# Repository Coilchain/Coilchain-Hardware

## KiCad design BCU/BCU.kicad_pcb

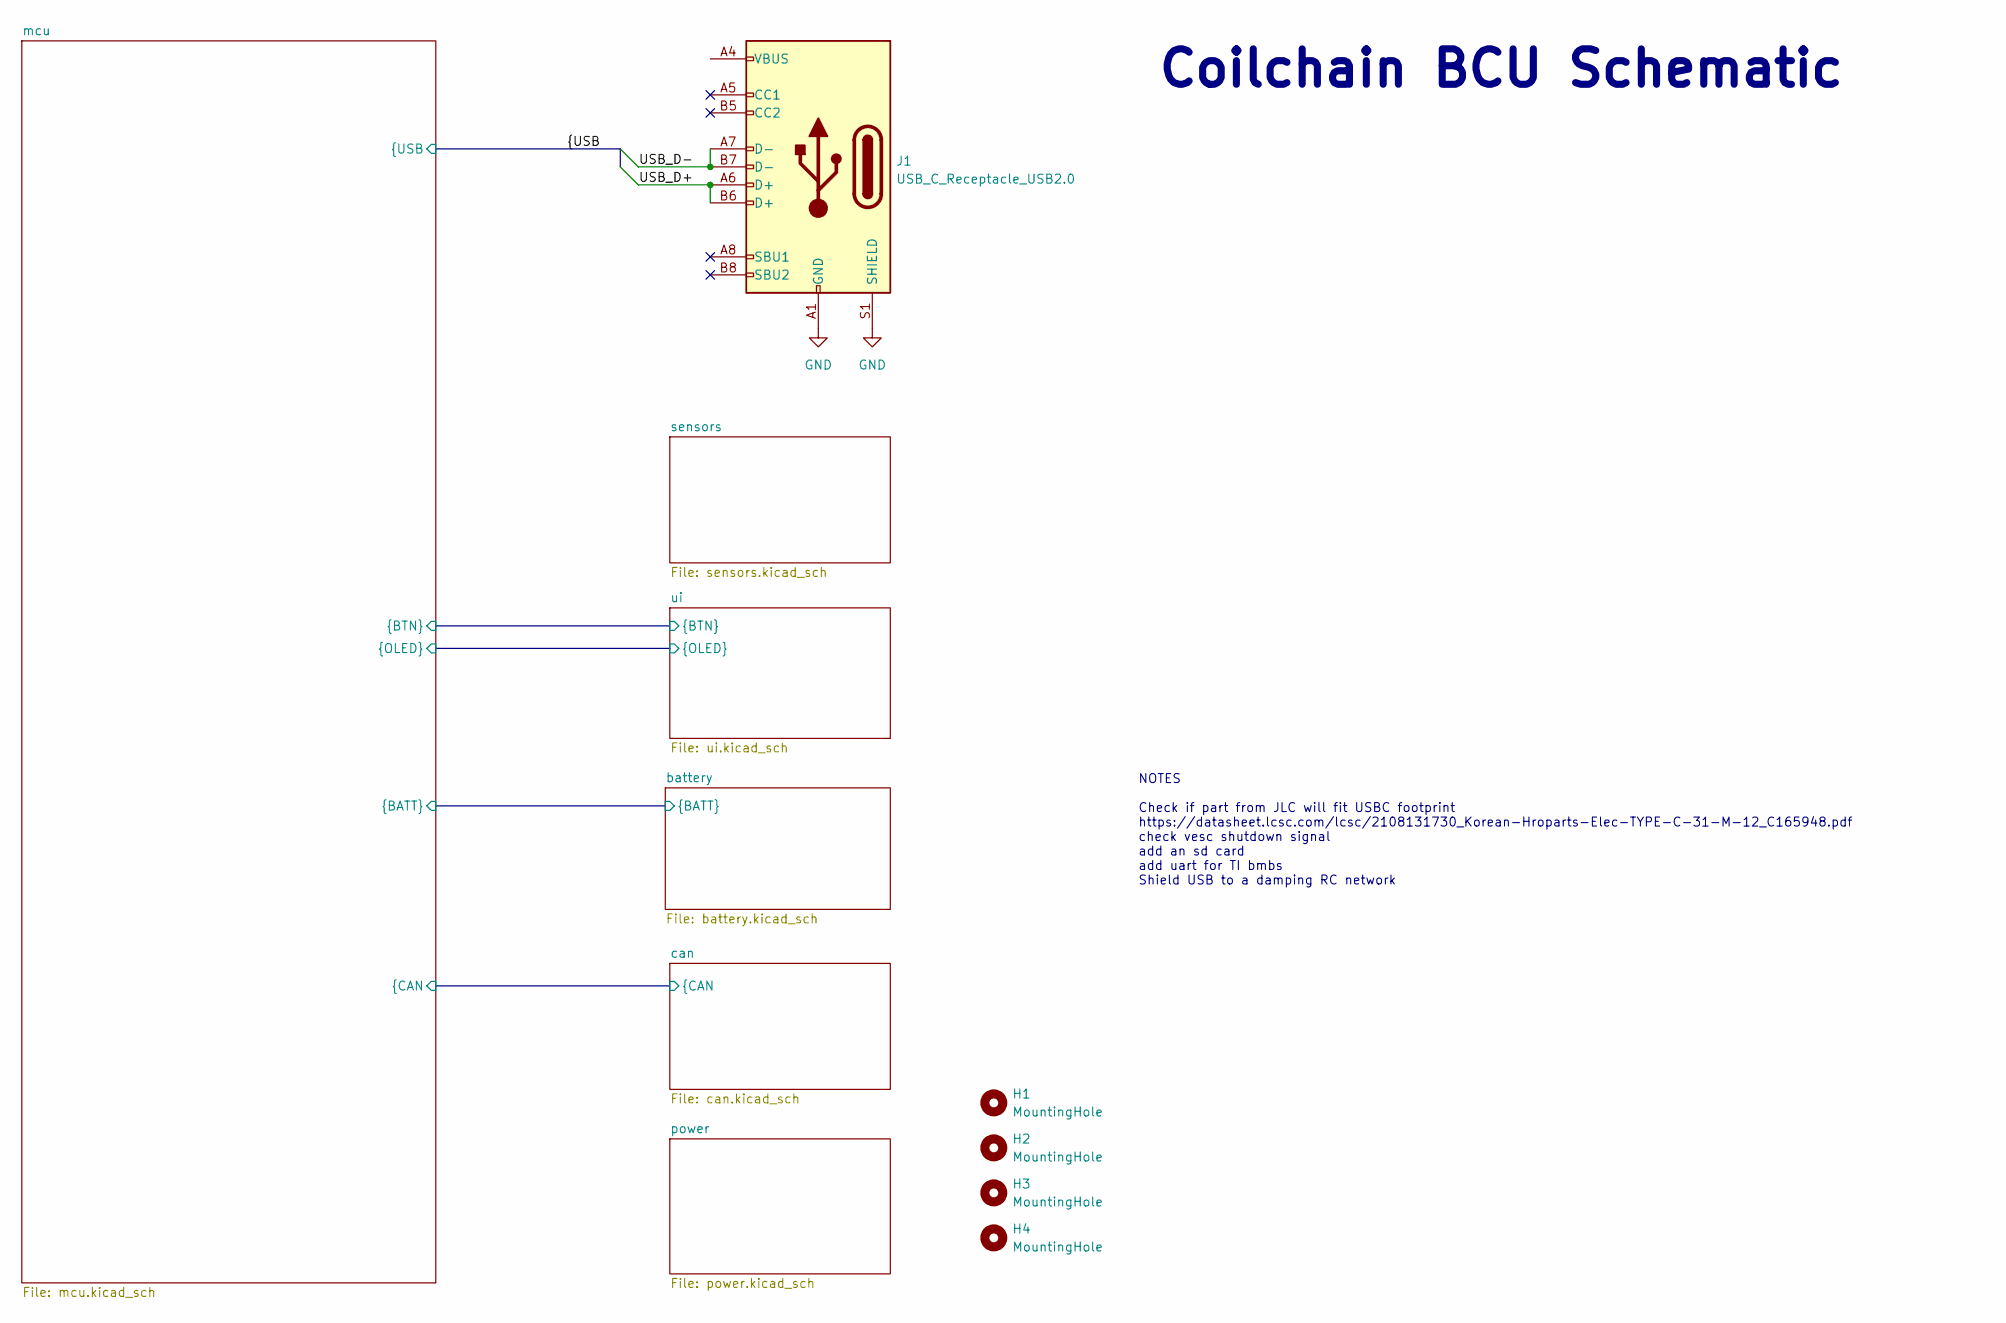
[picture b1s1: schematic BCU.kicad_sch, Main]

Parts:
H1, H2, H3, H4: MountingHole; MountingHole_2.2mm_M2
J1: USB_C_Receptacle_USB2.0; USB_C_Receptacle_HRO_TYPE-C-31-M-12

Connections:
/USB_D+: J1.A6 (D+), J1.B6 (D+)
/USB_D-: J1.A7 (D-), J1.B7 (D-)
GND: J1.A1 (GND), J1.A12 (GND), J1.B1 (GND), J1.B12 (GND), J1.S1 (SHIELD); also elsewhere on the board
unnamed: J1.A4 (VBUS), J1.A9 (VBUS), J1.B4 (VBUS), J1.B9 (VBUS)

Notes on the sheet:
Coilchain BCU Schematic
NOTES Check if part from JLC will fit USBC footprint https://datasheet.lcsc.com/lcsc/2108131730_Korean-Hroparts-Elec-TYPE-C-31-M-12_C165948.pdf check vesc shutdown signal add an sd card add uart for TI bmbs Shield USB to a damping RC network

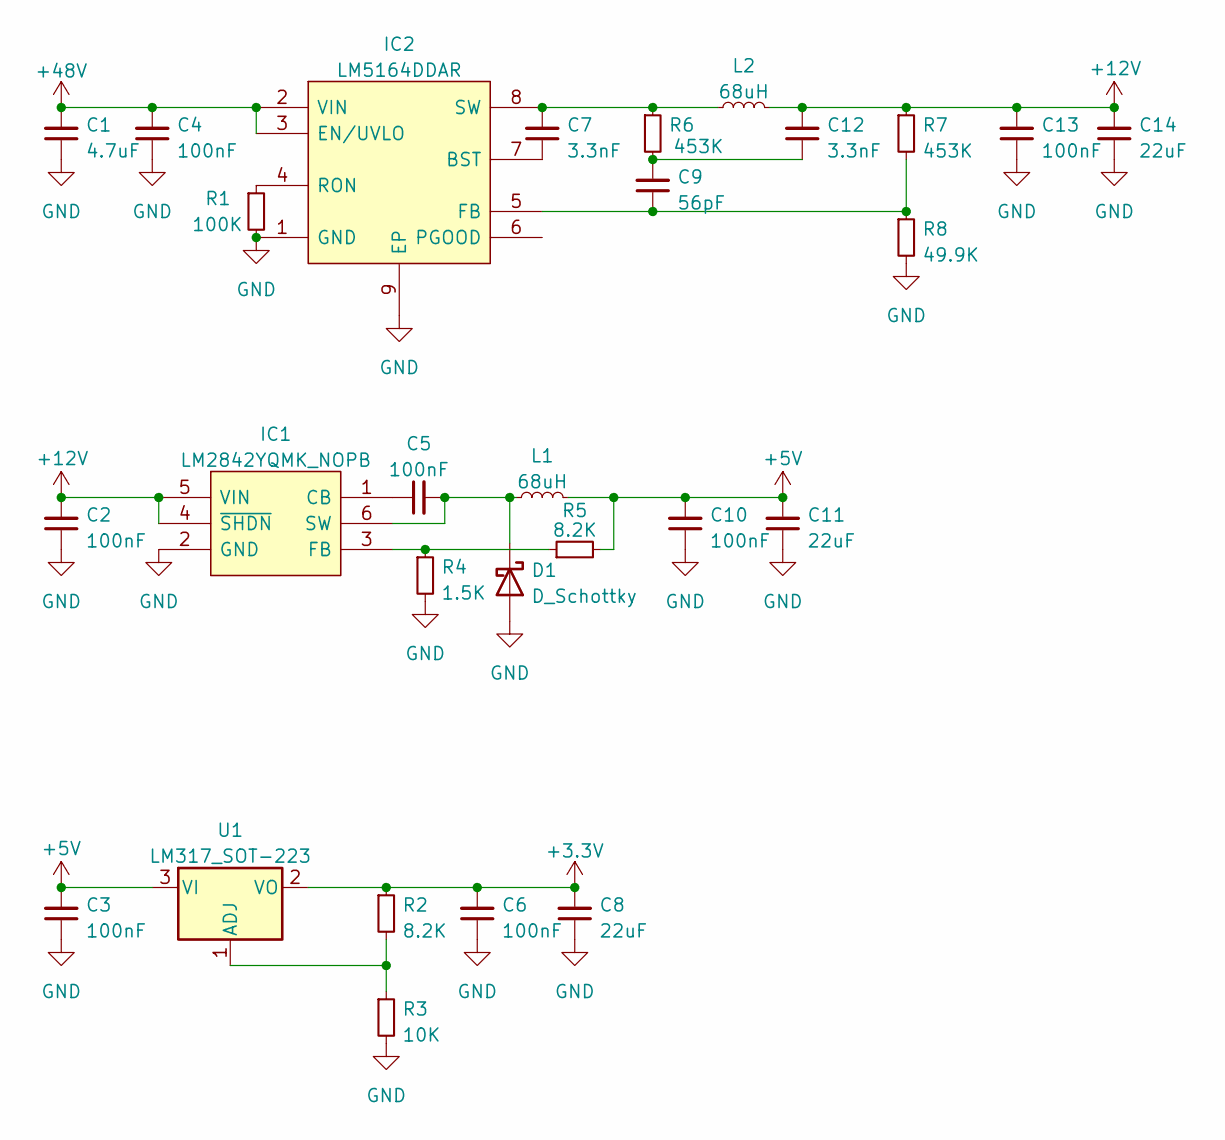
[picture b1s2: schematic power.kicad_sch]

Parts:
C1: 4.7uF; C_0603_1608Metric_Pad1.08x0.95mm_HandSolder
C2, C3, C4, C5, C6, C10, C13: 100nF; C_0402_1005Metric_Pad0.74x0.62mm_HandSolder
C7, C12: 3.3nF; C_0402_1005Metric_Pad0.74x0.62mm_HandSolder
C8, C11, C14: 22uF; C_0805_2012Metric_Pad1.18x1.45mm_HandSolder
C9: 56pF; C_0402_1005Metric_Pad0.74x0.62mm_HandSolder
D1: D_Schottky
IC1: LM2842YQMK_NOPB; SuperSOT-6; Manufacturer_Part_Number LM2842YQMK/NOPB; Mouser Part Number 926-LM2842YQMK/NOPB
IC2: LM5164DDAR; Texas_R-PDSO-G8_EP2.95x4.9mm_Mask2.4x3.1mm_ThermalVias; Manufacturer_Part_Number LM5164DDAR; Mouser Part Number 595-LM5164DDAR
L1: 68uH; L_1210_3225Metric_Pad1.42x2.65mm_HandSolder
L2: 68uH; L_TDK_SLF7045
R1: 100K; R_0402_1005Metric_Pad0.72x0.64mm_HandSolder
R2, R5: 8.2K; R_0402_1005Metric_Pad0.72x0.64mm_HandSolder
R3: 10K; R_0402_1005Metric_Pad0.72x0.64mm_HandSolder
R4: 1.5K; R_0402_1005Metric_Pad0.72x0.64mm_HandSolder
R6, R7: 453K; R_0402_1005Metric_Pad0.72x0.64mm_HandSolder
R8: 49.9K; R_0402_1005Metric_Pad0.72x0.64mm_HandSolder
U1: LM317_SOT-223; SOT-223-3_TabPin2

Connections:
+3V3: C6.2, C8.2, R2.1, U1.2 (VO); also elsewhere on the board
+5V: C3.2, C10.2, C11.2, L1.2, R5.2, U1.3 (VI); also elsewhere on the board
+12V: C2.2, C12.2, C13.2, C14.2, IC1.4 (~SHDN), IC1.5 (VIN), L2.2, R7.1
+48V: C1.2, C4.2, IC2.2 (VIN), IC2.3 (EN/UVLO)
GND: C1.1, C2.1, C3.1, C4.1, C6.1, C8.1, C10.1, C11.1, C13.1, C14.1, D1.2 (A), IC1.2 (GND), IC2.1 (GND), IC2.9 (EP), R1.2, R3.2, R4.2, R8.2; also elsewhere on the board
unnamed: C5.1, IC1.1 (CB)
unnamed: C5.2, D1.1 (K), IC1.6 (SW), L1.1
unnamed: C7.1, IC2.7 (BST)
unnamed: C7.2, IC2.8 (SW), L2.1, R6.1
unnamed: C9.1, IC2.5 (FB), R7.2, R8.1
unnamed: C9.2, C12.1, R6.2
unnamed: IC2.4 (RON), R1.1
unnamed: R2.2, R3.1, U1.1 (ADJ)
unnamed: IC1.3 (FB), R4.1, R5.1

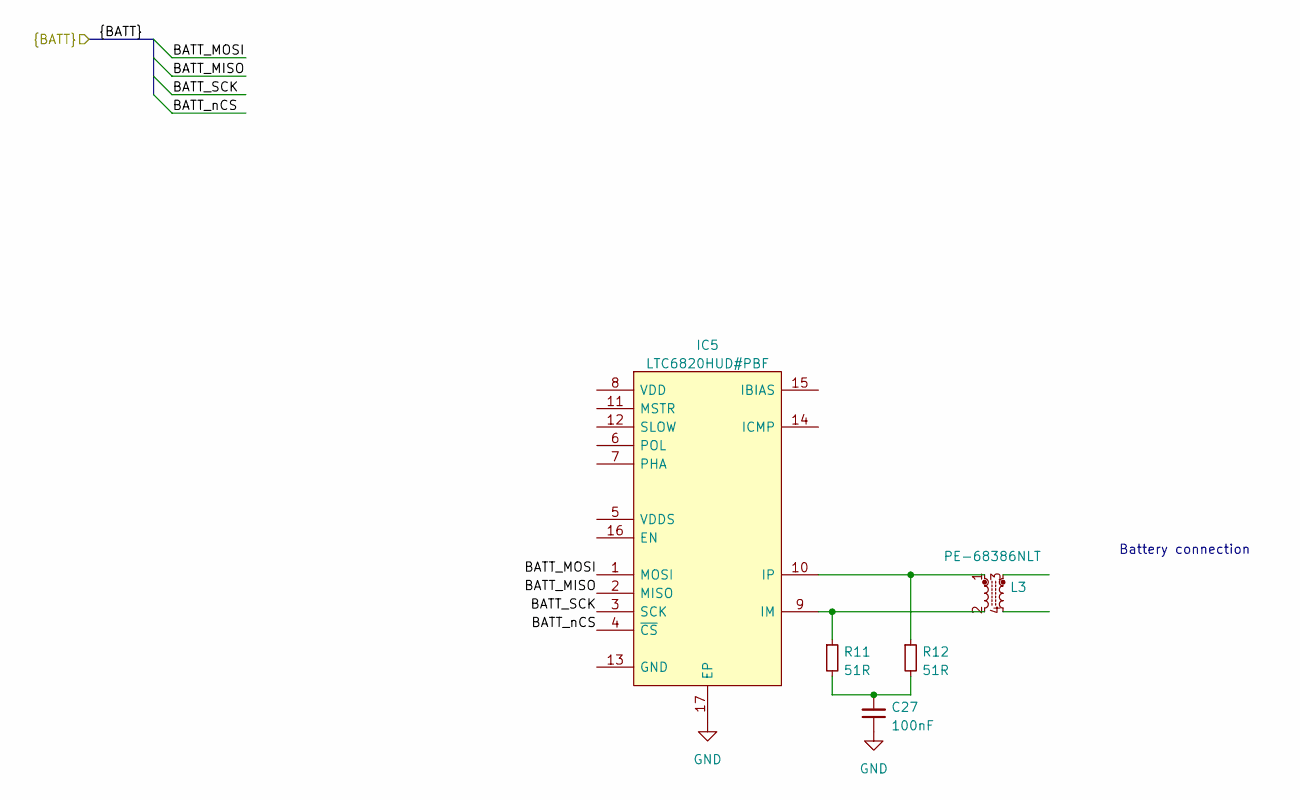
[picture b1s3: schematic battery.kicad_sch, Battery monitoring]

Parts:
C27: 100nF; C_0402_1005Metric_Pad0.74x0.62mm_HandSolder
IC5: LTC6820HUD#PBF; QFN-16-1EP_3x3mm_P0.5mm_EP1.7x1.7mm; Manufacturer_Part_Number LTC6820HUD#PBF; Mouser Part Number 584-LTC6820HUD#PBF
L3: PE-68386NLT
R11, R12: 51R; R_0402_1005Metric_Pad0.72x0.64mm_HandSolder

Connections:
/battery/BATT_MISO: IC5.2 (MISO)
/battery/BATT_MOSI: IC5.1 (MOSI)
/battery/BATT_SCK: IC5.3 (SCK)
/battery/BATT_nCS: IC5.4 (~CS)
GND: C27.1, IC5.17 (EP); also elsewhere on the board
unnamed: C27.2, R11.2, R12.2
unnamed: IC5.9 (IM), L3.2, R11.1
unnamed: IC5.10 (IP), L3.1, R12.1

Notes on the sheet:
Battery connection

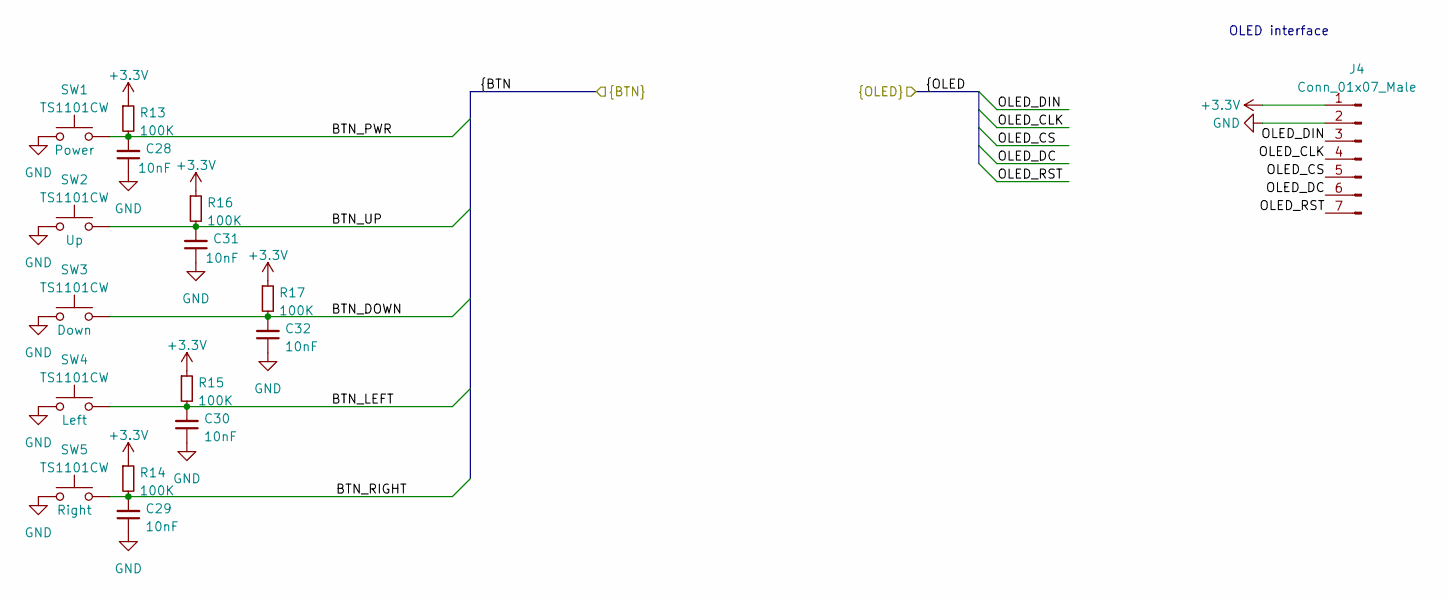
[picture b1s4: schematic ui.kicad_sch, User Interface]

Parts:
C28, C29, C30, C31, C32: 10nF; C_0402_1005Metric_Pad0.74x0.62mm_HandSolder
J4: Conn_01x07_Male; PinHeader_1x07_P2.54mm_Vertical
R13, R14, R15, R16, R17: 100K; R_0402_1005Metric_Pad0.72x0.64mm_HandSolder
SW1, SW2, SW3, SW4, SW5: TS1101CW; TS-1101-C-W

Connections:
+3V3: J4.1, R13.1, R14.1, R15.1, R16.1, R17.1; also elsewhere on the board
/mcu/BTN_DOWN: C32.2, R17.2, SW3.2; also elsewhere on the board
/mcu/BTN_LEFT: C30.2, R15.2, SW4.2; also elsewhere on the board
/mcu/BTN_PWR: C28.2, R13.2, SW1.2; also elsewhere on the board
/mcu/BTN_RIGHT: C29.2, R14.2, SW5.2; also elsewhere on the board
/mcu/BTN_UP: C31.2, R16.2, SW2.2; also elsewhere on the board
/mcu/OLED_CLK: J4.4; also elsewhere on the board
/mcu/OLED_CS: J4.5; also elsewhere on the board
/mcu/OLED_DC: J4.6; also elsewhere on the board
/mcu/OLED_DIN: J4.3; also elsewhere on the board
/mcu/OLED_RST: J4.7; also elsewhere on the board
GND: C28.1, C29.1, C30.1, C31.1, C32.1, J4.2, SW1.1, SW2.1, SW3.1, SW4.1, SW5.1; also elsewhere on the board

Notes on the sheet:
OLED interface

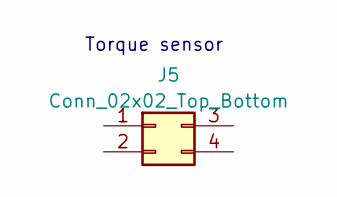
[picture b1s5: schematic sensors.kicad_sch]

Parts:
J5: Conn_02x02_Top_Bottom

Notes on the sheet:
Torque sensor

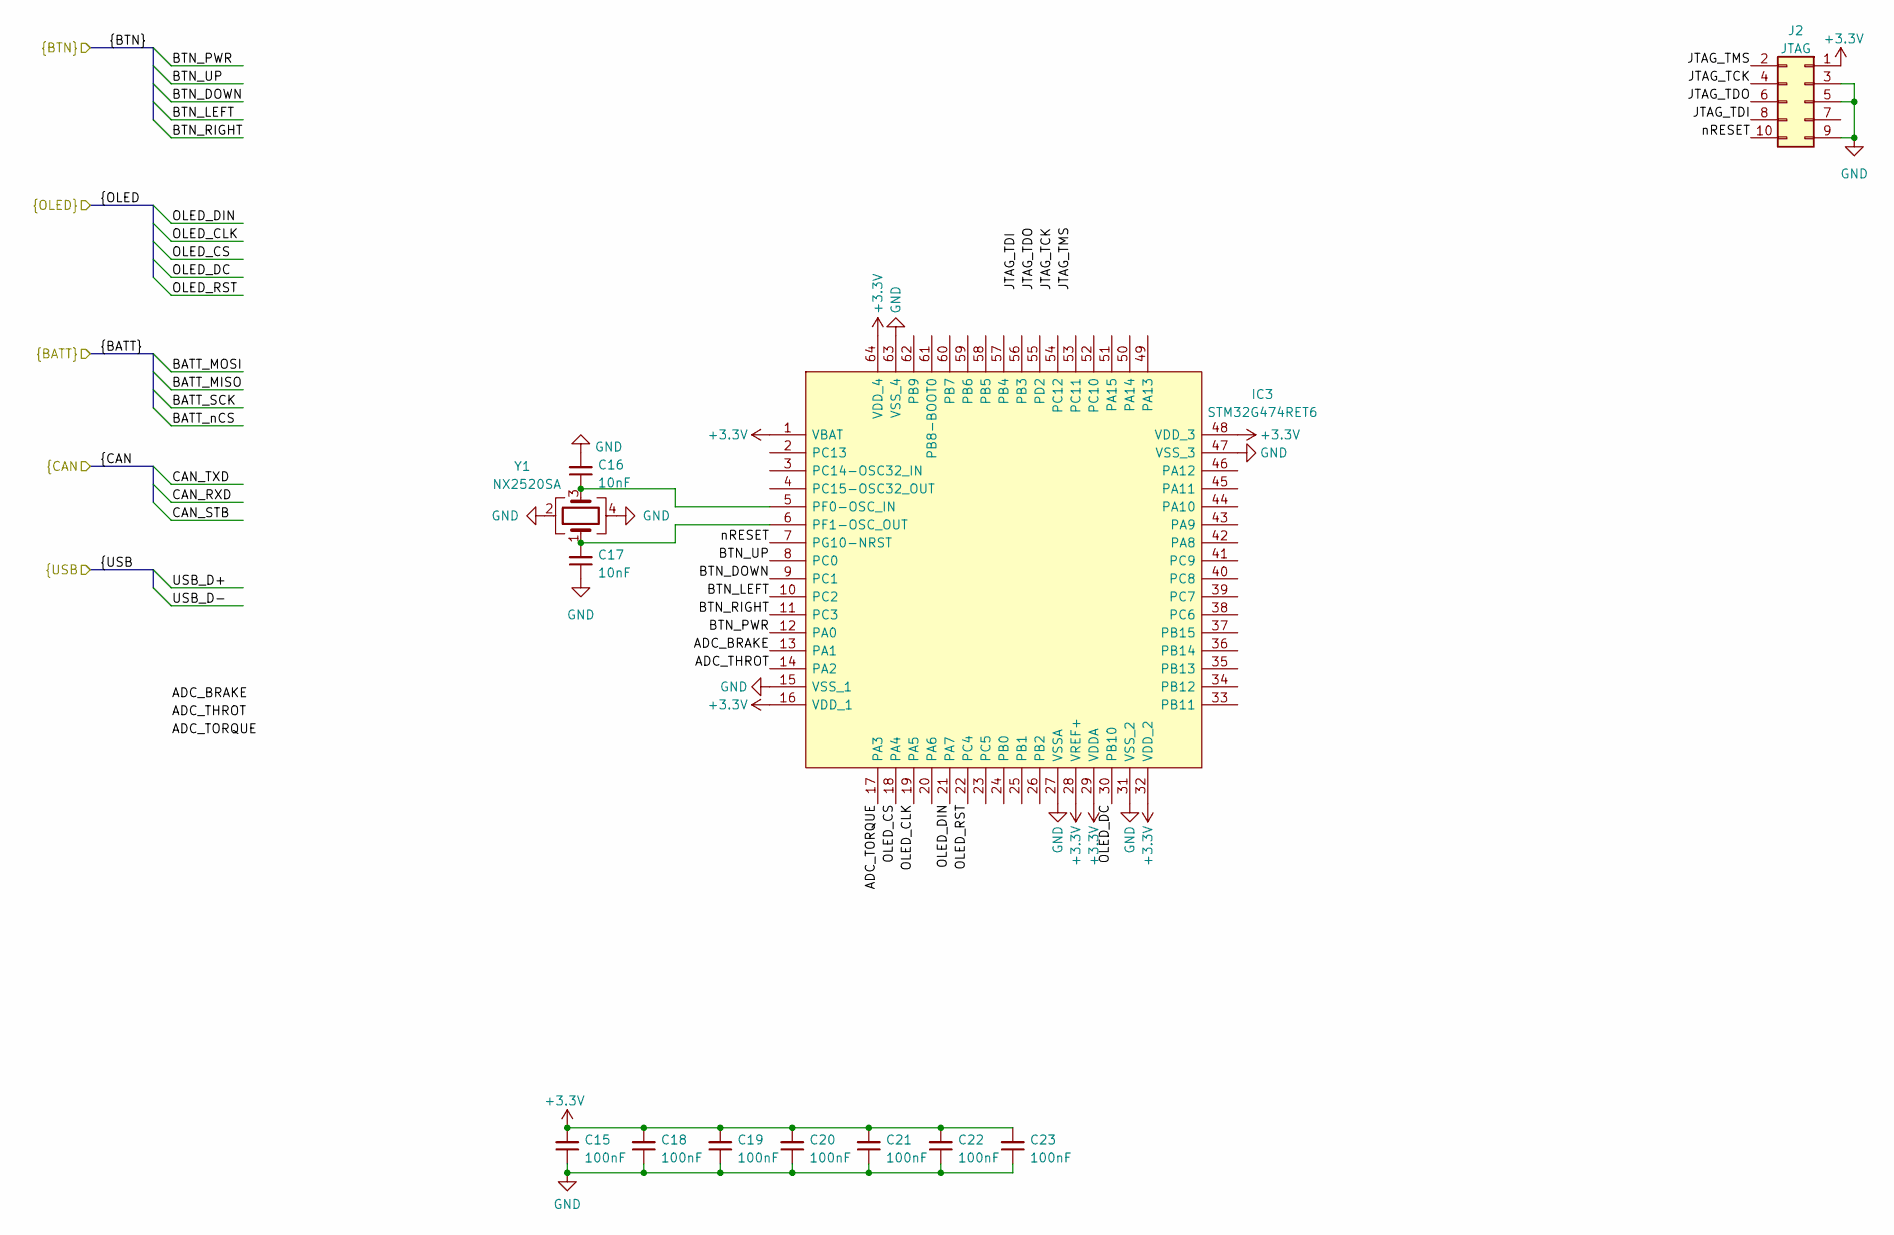
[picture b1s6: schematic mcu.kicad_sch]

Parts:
C15, C18, C19, C20, C21, C22, C23: 100nF; C_0402_1005Metric_Pad0.74x0.62mm_HandSolder
C16, C17: 10nF; C_0402_1005Metric_Pad0.74x0.62mm_HandSolder
IC3: STM32G474RET6; LQFP-64_10x10mm_P0.5mm; Manufacturer_Part_Number STM32G474RET6; Mouser Part Number 511-STM32G474RET6
J2: JTAG; PinHeader_2x05_P1.27mm_Vertical_SMD
Y1: NX2520SA; Crystal_SMD_2520-4Pin_2.5x2.0mm

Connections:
+3V3: C15.2, C18.2, C19.2, C20.2, C21.2, C22.2, C23.2, IC3.1 (VBAT), IC3.16 (VDD_1), IC3.28 (VREF+), IC3.29 (VDDA), IC3.32 (VDD_2), IC3.48 (VDD_3), IC3.64 (VDD_4), J2.1; also elsewhere on the board
/mcu/ADC_BRAKE: IC3.13 (PA1)
/mcu/ADC_THROT: IC3.14 (PA2)
/mcu/ADC_TORQUE: IC3.17 (PA3)
/mcu/BTN_DOWN: IC3.9 (PC1); also elsewhere on the board
/mcu/BTN_LEFT: IC3.10 (PC2); also elsewhere on the board
/mcu/BTN_PWR: IC3.12 (PA0); also elsewhere on the board
/mcu/BTN_RIGHT: IC3.11 (PC3); also elsewhere on the board
/mcu/BTN_UP: IC3.8 (PC0); also elsewhere on the board
/mcu/JTAG_TCK: J2.4
/mcu/JTAG_TDI: J2.8
/mcu/JTAG_TDO: J2.6
/mcu/JTAG_TMS: J2.2
/mcu/OLED_CLK: IC3.19 (PA5); also elsewhere on the board
/mcu/OLED_CS: IC3.18 (PA4); also elsewhere on the board
/mcu/OLED_DC: IC3.30 (PB10); also elsewhere on the board
/mcu/OLED_DIN: IC3.21 (PA7); also elsewhere on the board
/mcu/OLED_RST: IC3.22 (PC4); also elsewhere on the board
/mcu/nRESET: IC3.7 (PG10-NRST), J2.10
GND: C15.1, C16.2, C17.1, C18.1, C19.1, C20.1, C21.1, C22.1, C23.1, IC3.15 (VSS_1), IC3.27 (VSSA), IC3.31 (VSS_2), IC3.47 (VSS_3), IC3.63 (VSS_4), J2.3, J2.5, J2.9, Y1.2, Y1.4; also elsewhere on the board
unnamed: C16.1, IC3.5 (PF0-OSC_IN), Y1.3
unnamed: C17.2, IC3.6 (PF1-OSC_OUT), Y1.1

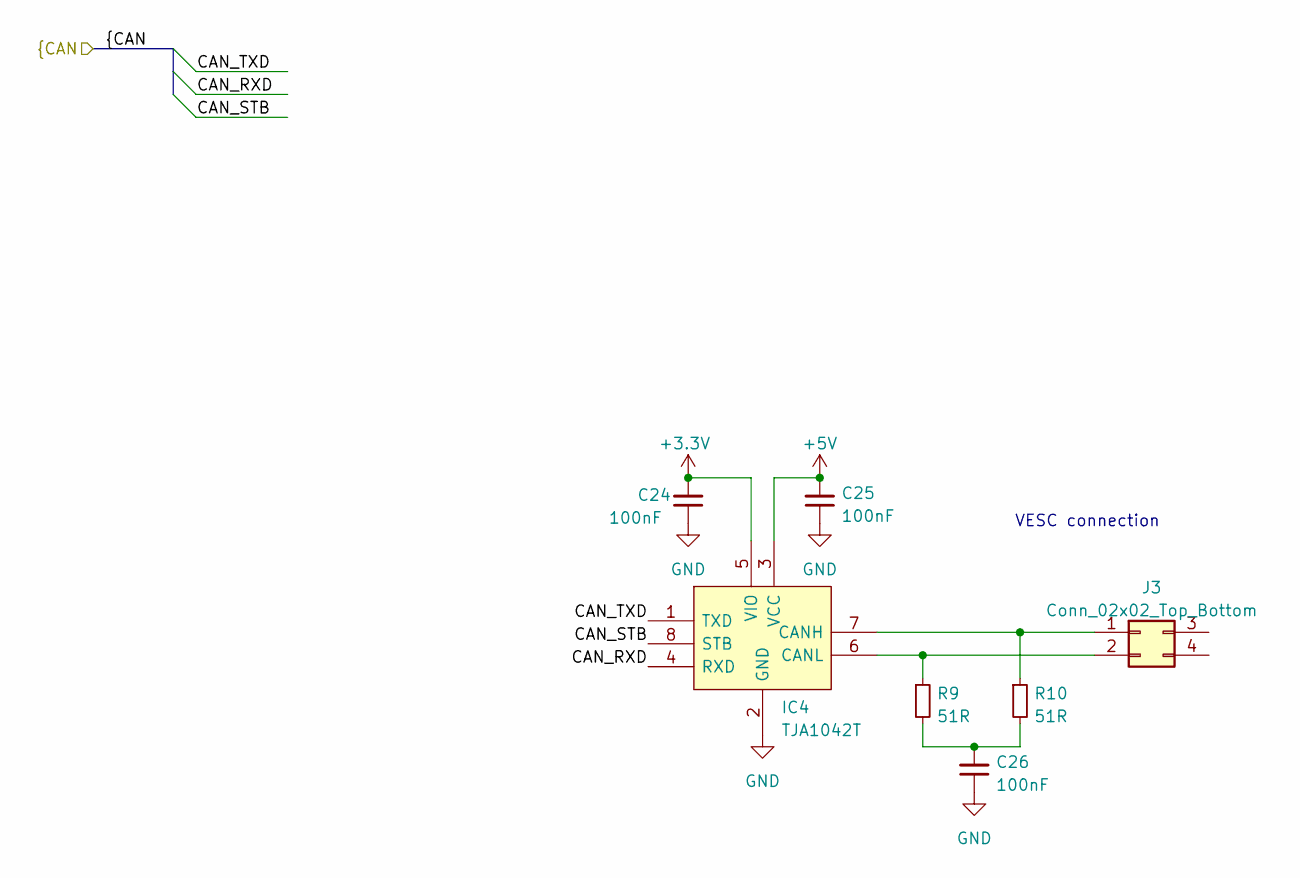
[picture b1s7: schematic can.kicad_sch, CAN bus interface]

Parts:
C24, C25, C26: 100nF; C_0402_1005Metric_Pad0.74x0.62mm_HandSolder
IC4: TJA1042T; SO-8_3.9x4.9mm_P1.27mm; Manufacturer_Part_Number TJA1042T/3,118; Mouser Part Number 771-TJA1042T3118
J3: Conn_02x02_Top_Bottom
R9, R10: 51R; R_0402_1005Metric_Pad0.72x0.64mm_HandSolder

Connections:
+3V3: C24.2, IC4.5 (VIO); also elsewhere on the board
+5V: C25.2, IC4.3 (VCC); also elsewhere on the board
/can/CAN_RXD: IC4.4 (RXD)
/can/CAN_STB: IC4.8 (STB)
/can/CAN_TXD: IC4.1 (TXD)
GND: C24.1, C25.1, C26.1, IC4.2 (GND); also elsewhere on the board
unnamed: C26.2, R9.2, R10.2
unnamed: IC4.6 (CANL), J3.2, R9.1
unnamed: IC4.7 (CANH), J3.1, R10.1

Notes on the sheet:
VESC connection

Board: 2 copper layers, 70 parts (60 on the bottom side), 36 nets, no tracks yet.

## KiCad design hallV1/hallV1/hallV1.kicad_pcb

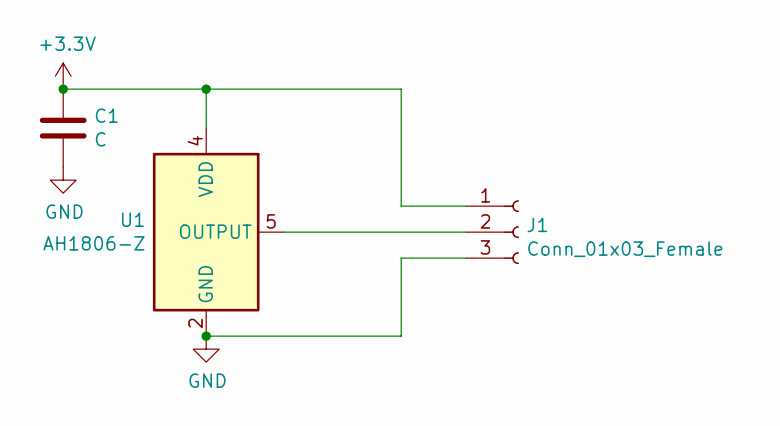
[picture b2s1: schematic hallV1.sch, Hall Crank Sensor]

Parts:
C1: C; C_0603_1608Metric
J1: Conn_01x03_Female; PinHeader_1x03_P2.54mm_Horizontal
U1: AH1806-Z; SOT-553

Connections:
+3V3: C1.1, J1.1, U1.4 (VDD)
GND: C1.2, J1.3, U1.2 (GND)
unnamed: J1.2, U1.5 (OUTPUT)

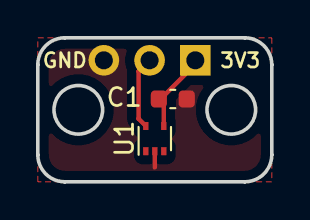
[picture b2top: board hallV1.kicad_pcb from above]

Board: 2 copper layers, 13.0 x 8.0 mm, 3 parts (1 on the bottom side), 3 nets.

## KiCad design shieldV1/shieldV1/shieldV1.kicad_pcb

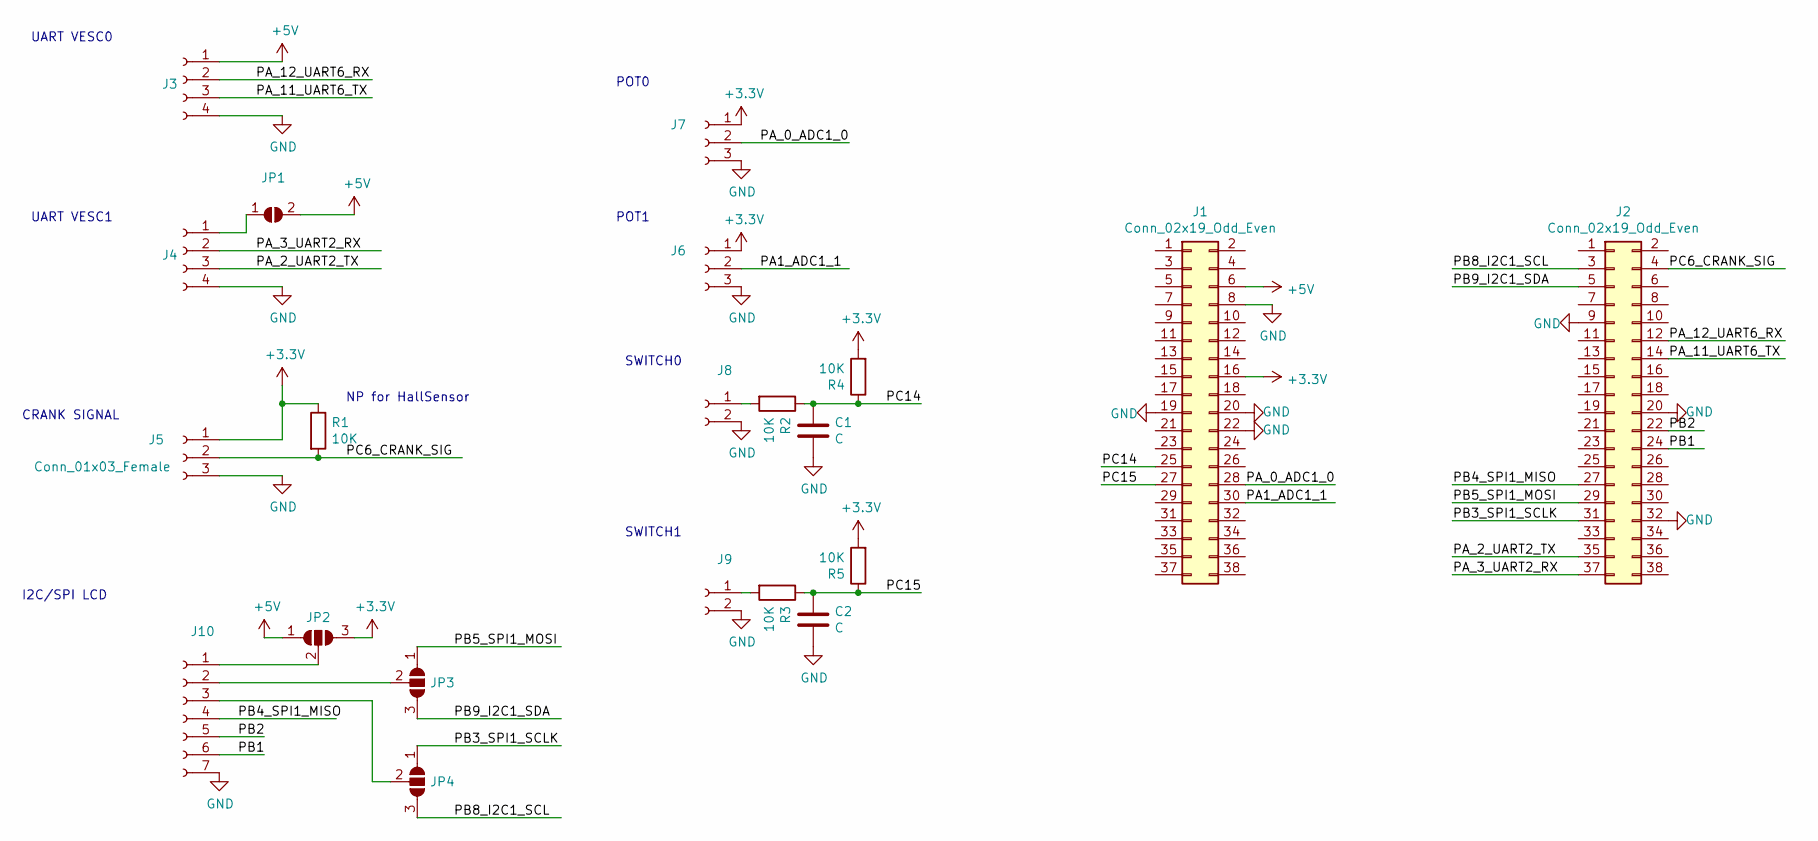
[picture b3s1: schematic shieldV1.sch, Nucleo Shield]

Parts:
C1, C2: C; C_0603_1608Metric
J1, J2: Conn_02x19_Odd_Even; PinSocket_2x19_P2.54mm_Vertical
J3, J4: Conn_01x04_Female; JST_GH_SM04B-GHS-TB_1x04-1MP_P1.25mm_Horizontal
J5, J6, J7: Conn_01x03_Female; JST_GH_SM03B-GHS-TB_1x03-1MP_P1.25mm_Horizontal
J8, J9: Conn_01x02_Female; JST_GH_SM02B-GHS-TB_1x02-1MP_P1.25mm_Horizontal
J10: Conn_01x07_Female; JST_GH_SM07B-GHS-TB_1x07-1MP_P1.25mm_Horizontal
JP1: SolderJumper_2_Open; SolderJumper-2_P1.3mm_Open_RoundedPad1.0x1.5mm
JP2, JP3, JP4: SolderJumper_3_Open; SolderJumper-3_P1.3mm_Open_RoundedPad1.0x1.5mm
R1, R2, R3, R4, R5: 10K; R_0603_1608Metric

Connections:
+3V3: J1.16, J5.1, J6.1, J7.1, JP2.3 (B), R1.1, R4.2, R5.2
+5V: J1.6, J3.1, JP1.2 (B), JP2.1 (A)
/PA1_ADC1_1: J1.30, J6.2
/PA_0_ADC1_0: J1.28, J7.2
/PA_2_UART2_TX: J2.35, J4.3
/PA_3_UART2_RX: J2.37, J4.2
/PA_11_UART6_TX: J2.14, J3.3
/PA_12_UART6_RX: J2.12, J3.2
/PB1: J2.24, J10.6
/PB2: J2.22, J10.5
/PB3_SPI1_SCLK: J2.31, JP4.1 (A)
/PB4_SPI1_MISO: J2.27, J10.4
/PB5_SPI1_MOSI: J2.29, JP3.1 (A)
/PB8_I2C1_SCL: J2.3, JP4.3 (B)
/PB9_I2C1_SDA: J2.5, JP3.3 (B)
/PC6_CRANK_SIG: J2.4, J5.2, R1.2
/PC14: C1.1, J1.25, R2.1, R4.1
/PC15: C2.1, J1.27, R3.1, R5.1
GND: C1.2, C2.2, J1.8, J1.19, J1.20, J1.22, J2.9, J2.20, J2.32, J3.4, J4.4, J5.3, J6.3, J7.3, J8.2, J9.2, J10.7
unnamed: J4.1, JP1.1 (A)
unnamed: J8.1, R2.2
unnamed: J9.1, R3.2
unnamed: J10.1, JP2.2 (C)
unnamed: J10.2, JP3.2 (C)
unnamed: J10.3, JP4.2 (C)

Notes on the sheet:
UART VESC0
UART VESC1
CRANK SIGNAL
NP for HallSensor
I2C/SPI LCD
SWITCH1
SWITCH0
POT1
POT0

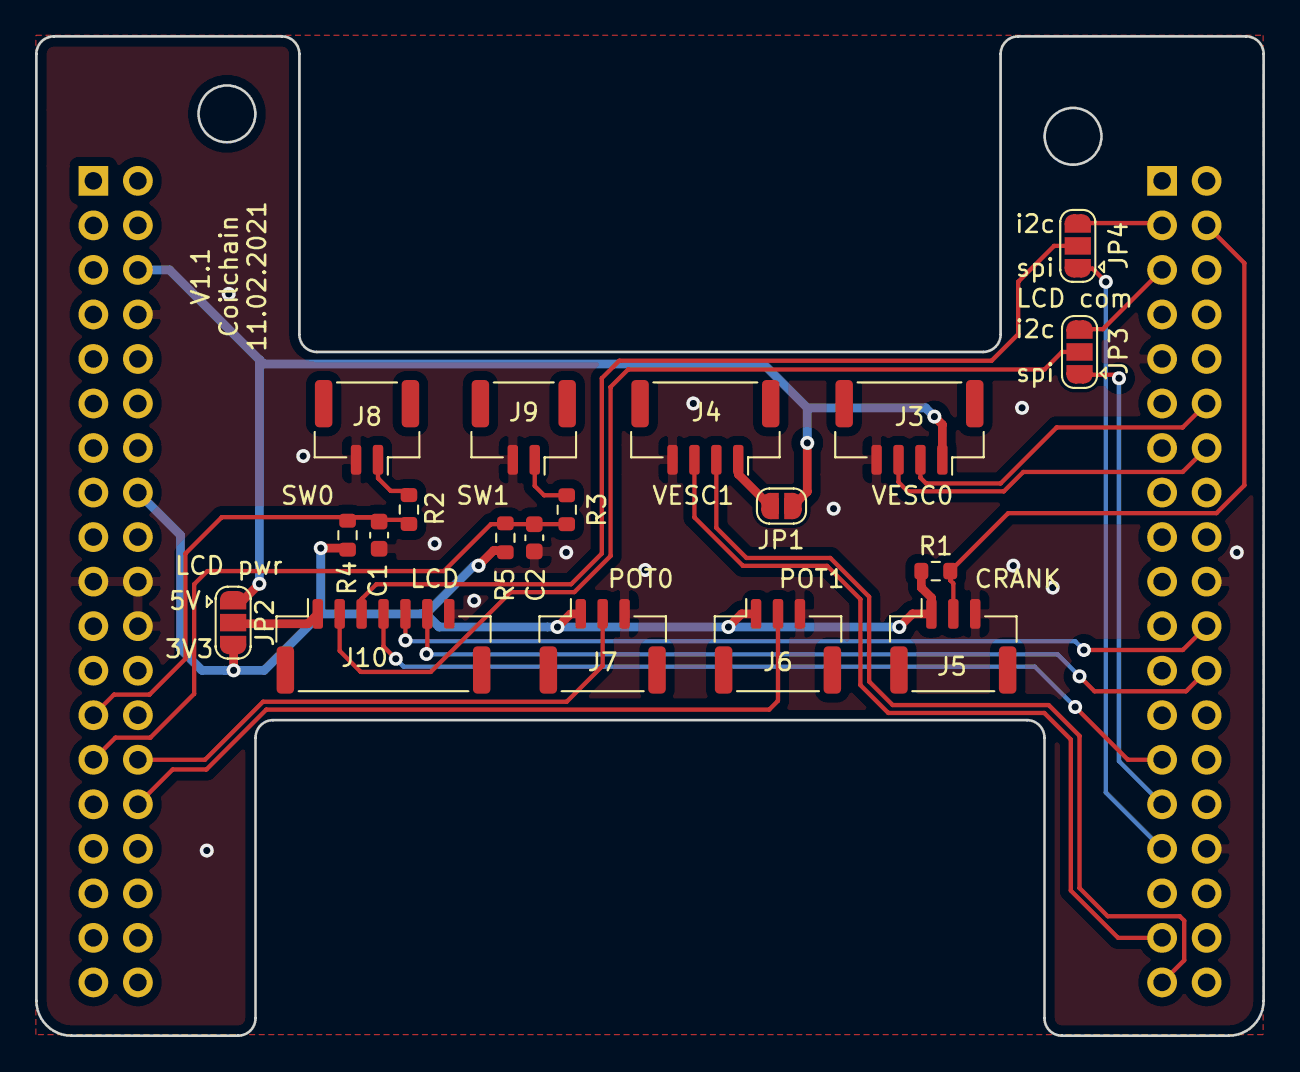
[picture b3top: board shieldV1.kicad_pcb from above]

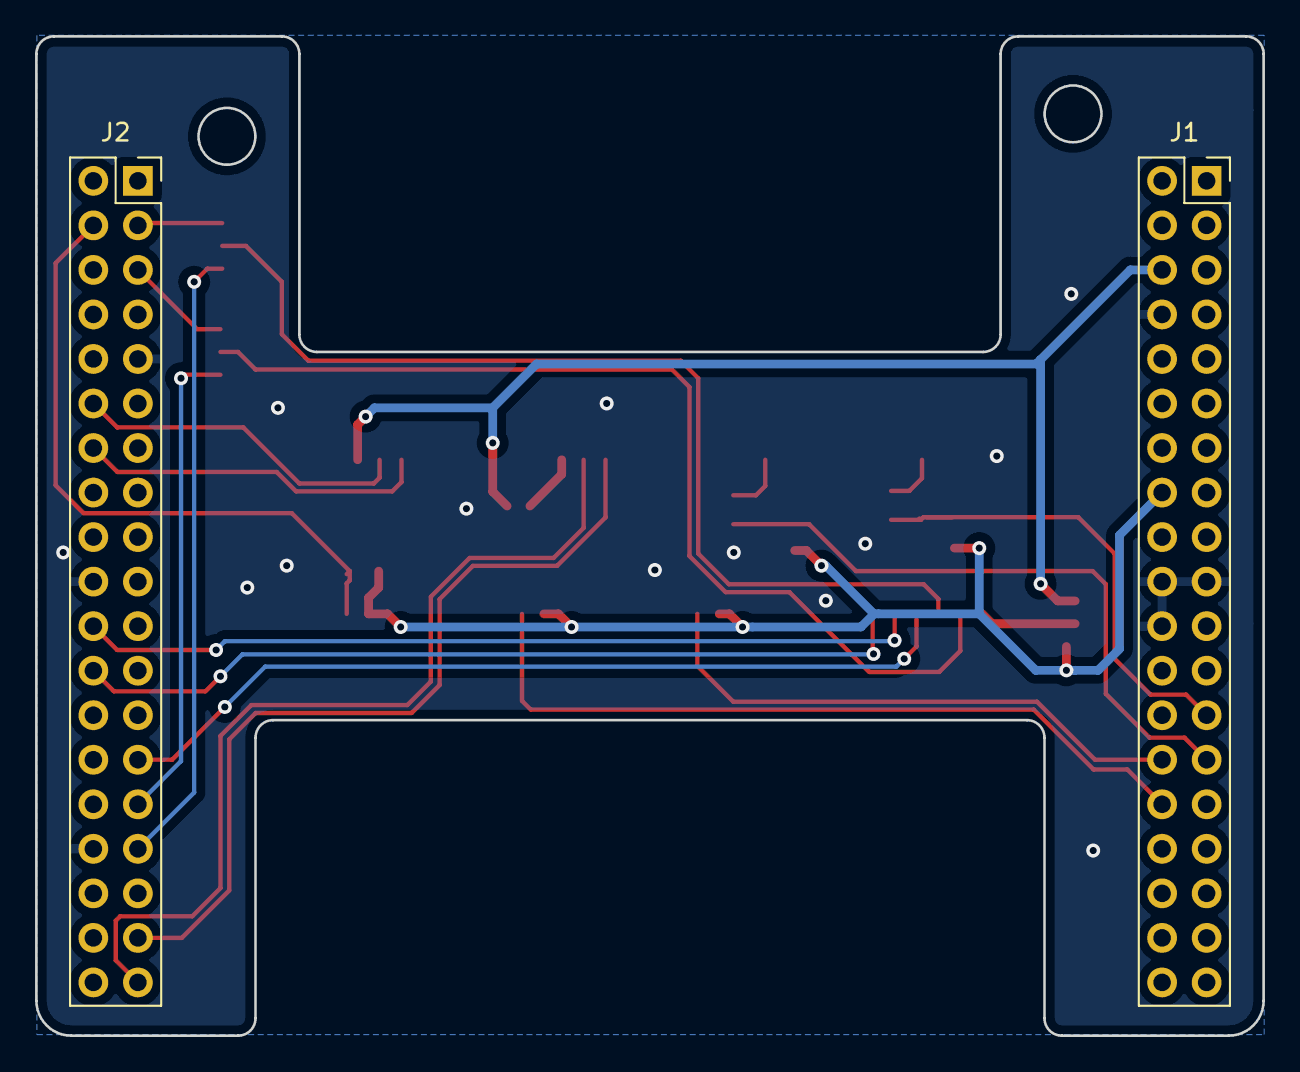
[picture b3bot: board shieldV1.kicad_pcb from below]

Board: 2 copper layers, 70.0 x 57.0 mm, 21 parts (2 on the bottom side), 25 nets.

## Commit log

2021-02-02 Initial import
2021-02-02 Modify GND symbol and crank signal wiring
2021-02-02 Chage JST to Horizontal
2021-02-02 Clean schematic wiring
2021-02-11 Add hall sensor PCB
2021-02-11 Add fab output
2021-02-11 Add shield fab output
2021-02-11 Change decoupling capacitor position
2021-02-11 Remove deprecated pdfs
2021-02-11 Add hall schematic pdf
2021-02-11 Add shield schematic
2021-02-11 Add hall 3D
2021-02-11 Add shield 3D
2022-05-14 New project for Bike Control Unit
2022-05-15 Added some more components
2022-05-15 Update BCU.kicad_sch
    placed and wired a few more symbols
2022-05-15 Create BCU.ioc
    STM32CubeMX project
2022-05-17 Add PCB outline
2022-05-17 Update BCU.kicad_sch
    wip
2022-05-20 Update BCU.kicad_sch
    added HV power supply
2022-05-21 update pcb+sch
    pushed to pcb
2022-05-22 Add BCU outline
2022-05-22 Add BCU outline with connector
2022-05-26 Migrate schemtaic to coilchain library
2022-05-26 Make rough component placement for evaluating missing 3D
2022-05-29 change 48v to +BATT, increase cap sizes
2022-06-05 Added power enable logic
